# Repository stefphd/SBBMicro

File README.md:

# Introduction

This repository contains the source code for the self-balancing-bike micro-controller unit (Teensy 4.1-based 🚀️).
The introduction shows the files and folders contained in this repository and how they are organized, the prerequisites necessary, and the procedures to be used in order to build and upload the code, to generate the documentation, and to automatically generate the control-algorithm code from the Simulink model (using matlab tools).

Windows is officially supported, although compilation is also implemented for Linux. MacOS is NOT supported. 

## Files

Files:

* `controlModel.slx`: control model implementation in Simulink
* `gencode.m`: MATLAB function for code generation from Simulink model
* `params.sldd`: Simulink parameters used in `controlModel.slx`
* `build_linux.sh`: build shell script for Linux
* `build_win.bat`: build shmell script for Windows
* `Doxyfile`: configuration file for documentation generation from source code using *doxygen*
* `Makefile`: makefile for building, uploading and documentation generation using *make*
* `startup.m`: startup file for MATLAB (just to add necessary path)
* `INSTALL_PREREQ.md`: guide for the installation of the pre-requisites
* `README.md`: readme file

Code folders:

* `./include`: contains `.h` files included in source code
* `./src`: contains source `.c` or `.cpp` files, including main file `main.cpp`
* `./lib`: contains a folder for each used library, with file `library.properties` for defining the library properties (mandatory for arduino compiling) and `.h` and `.cpp` files (possibly contained in folder `./src/`)
* `./tools/teensy`: contains the core code for the Teensy microcontroller

Additional folders:

* `./tools/teensy-windows`: build tools for Windows
* `./tools/teensy-linux`: build tools for Linux
* `./docs/html`: contains the documentation in html (generated automatically from source code using *doxygen*)
* `./docs/extra`: contains extra documentation (user-written), which is included using *doxygen*
* `./matlab-tools`: contains matlab tools usefull for code generation and other stuff
* `./hardware`: contains the kicad project files
* `./.vscode`: contains VS code property file(s)
* `./.build` and `.cache`: hidden folders created only during compilation

## Pre-requisites

* *MATLAB/Simulink* with the *Embedded Coder Toolbox* installed (>=2021a), for control algorithm code generation only

No other dependecies are necessary: all used libraries are already included in `./lib/`.

Additional utilities (only recommended):

* *make* to build using the `Makefile`; alternativelly, shell or MATLAV scripts can be used
* *Visual Studio Code* with *C/C++* extension for code completation
* *Doxygen* to generate the documentation
* *KiCad* to open the schematic files in `./hardware`

See the installation guide for the pre-requisites for details.

## Documentation

Documentation for the source code and the user-defined libraries (but not for other third-party libraries) can be generated from the source using *Doxygen* with

```bash
doxygen
```

or using *make*

```bash
make doc
```

Generated documentation includes only a html version in `./docs/html`, with main file `index.html`. Documentation is also available on <https://stefphd.github.io/SBBMicro/>.
A latex documentation may be also generated by setting

```doxygen
GENERATE_LATEX  = YES
```

in `Doxyfile`. The latex version will be in `./docs/latex`, and can be compiled using latex with

```bash
cd ./docs/latex
make
```

which generates the pdf file `./doc/latex/refman.pdf`.

\attention Latex documentation requires having both *latex* and *make* installed.

## Code generation

Code generation of the control algorithm is performed via *MATLAB/Simulink* with the *Embedded Coder Toolbox*. Other toolboxes may be required. Code generation can be launch with *MATLAB* using

```MATLAB
startup;
gencode
```

The general usage of this function is

```MATLAB
startup;
gencode(modelname,dest_dir);
```

where `modelname` is the name of the Simulink model (without the `*.slx` extension included), while `dest_dir` is the destination directory: generated code is placed in `./dest_dir/modelname/src`. If no modelname is given, the function uses the first `*.slx` file found in the current directory. If no destination directory is given, the functions uses `./lib`. Code generation may be also performed using *make*, however this may take some time.

\note Toolboxes required by the code generation can be shown by running in MATLAB

```MATLAB
startup;
check_toolbox();
```

\attention For a correct usage in this project the above functions should be run in the main directory, and not in `./matlab-tools/`.

## Building

Compilation is performed using the *arduino-builder*. Bash scripts provide simple usage depending on the operative system:

* Linux:
  
  ```bash
  ./build_linux.sh
  ```
  
  or
  
  ```bash
  bash build_linux.sh
  ```
  
  \note Tested with Arch-Linux x64.

* Windows:
  
  ```bash
  ./build_win.bat
  ```
  
  \note Tested with Windows 10 x64.

* MacOS: not implemented yet, however it should be similar to Linux.

Alternatively, one can use `ctrl+shift+B` to build the code in *Visual Studio Code* with both Linux and Windows (this makes use of `build_linux.sh` or `build_win.sh` depending on the operative system). One may also use *make* the building and uploading.

\note The above shell scripts perform both the building and the uploading: it is not possible to build or upload only.

## Make tools

One may also use *make* for the building, uploading and the documentation generation. This allows several operations using similar syntax, so as to perform single operations at a time:

* `make` or `make all` to build and upload the code.
* `make build` to build the code only
* `make upload` to upload code only
* `make clean` to clean the build and cache directories
* `make remake` to clean, build and upload the code
* `make rebuild` to clean and rebuild
* `make doc` to build the documentation
* `make cleandoc` to clean the documentation
* `make help` to print the Makefile help

\note The above commands can be also used at the same time, e.g. `make build doc` to build and generate the documentation.

## MATLAB make

As an alternative to `make` and `gencode`, the code generation, buiding, uploading and documentation generation may be also performed at the same time from within the MATLAB command window. This employs a MATLAB function name `make` in `./matlab-tool/`. The function must be used inside MATLAB with the following syntax:

* `make all` or just `make` to generate code from the Simulink model, build and upload

* `make gencode` to generate the code only from the Simulink model. Note that this corresponds to call `gencode` with no input arguments, i.e. the first `*.slx` file found is used

* `make build` to build the code

* `make upload` to upload the code

* `make clean` to clean the build and cache directories

* `make remake` to clean, build and upload the code

* `make rebuild` to clean and rebuild

* `make doc` to build the documentation

* `make cleandoc` to clean the documentation

* `make help` to print the help.

\note Note that this function emulates the function `gencode` and the standard `make` commands. However, it does not require having `make` installed but only `doxygen` for the generation of the documentation.

\note The above commands can be also used at the same time, e.g. `make build doc` to build and generate the documentation.

## Known issues

* Undefined identifiers found by Visual Studio Code, however this is only a C/C++ IntelliSense issue (compilation works fine)

\todo Doc: Documentaton for Simuling and code generation???
\todo Make Arduino functions working in Simulink when compiling (maybe declare Arduino functions as external in Simulink, so as the linker links them)
\todo To implement brake motor

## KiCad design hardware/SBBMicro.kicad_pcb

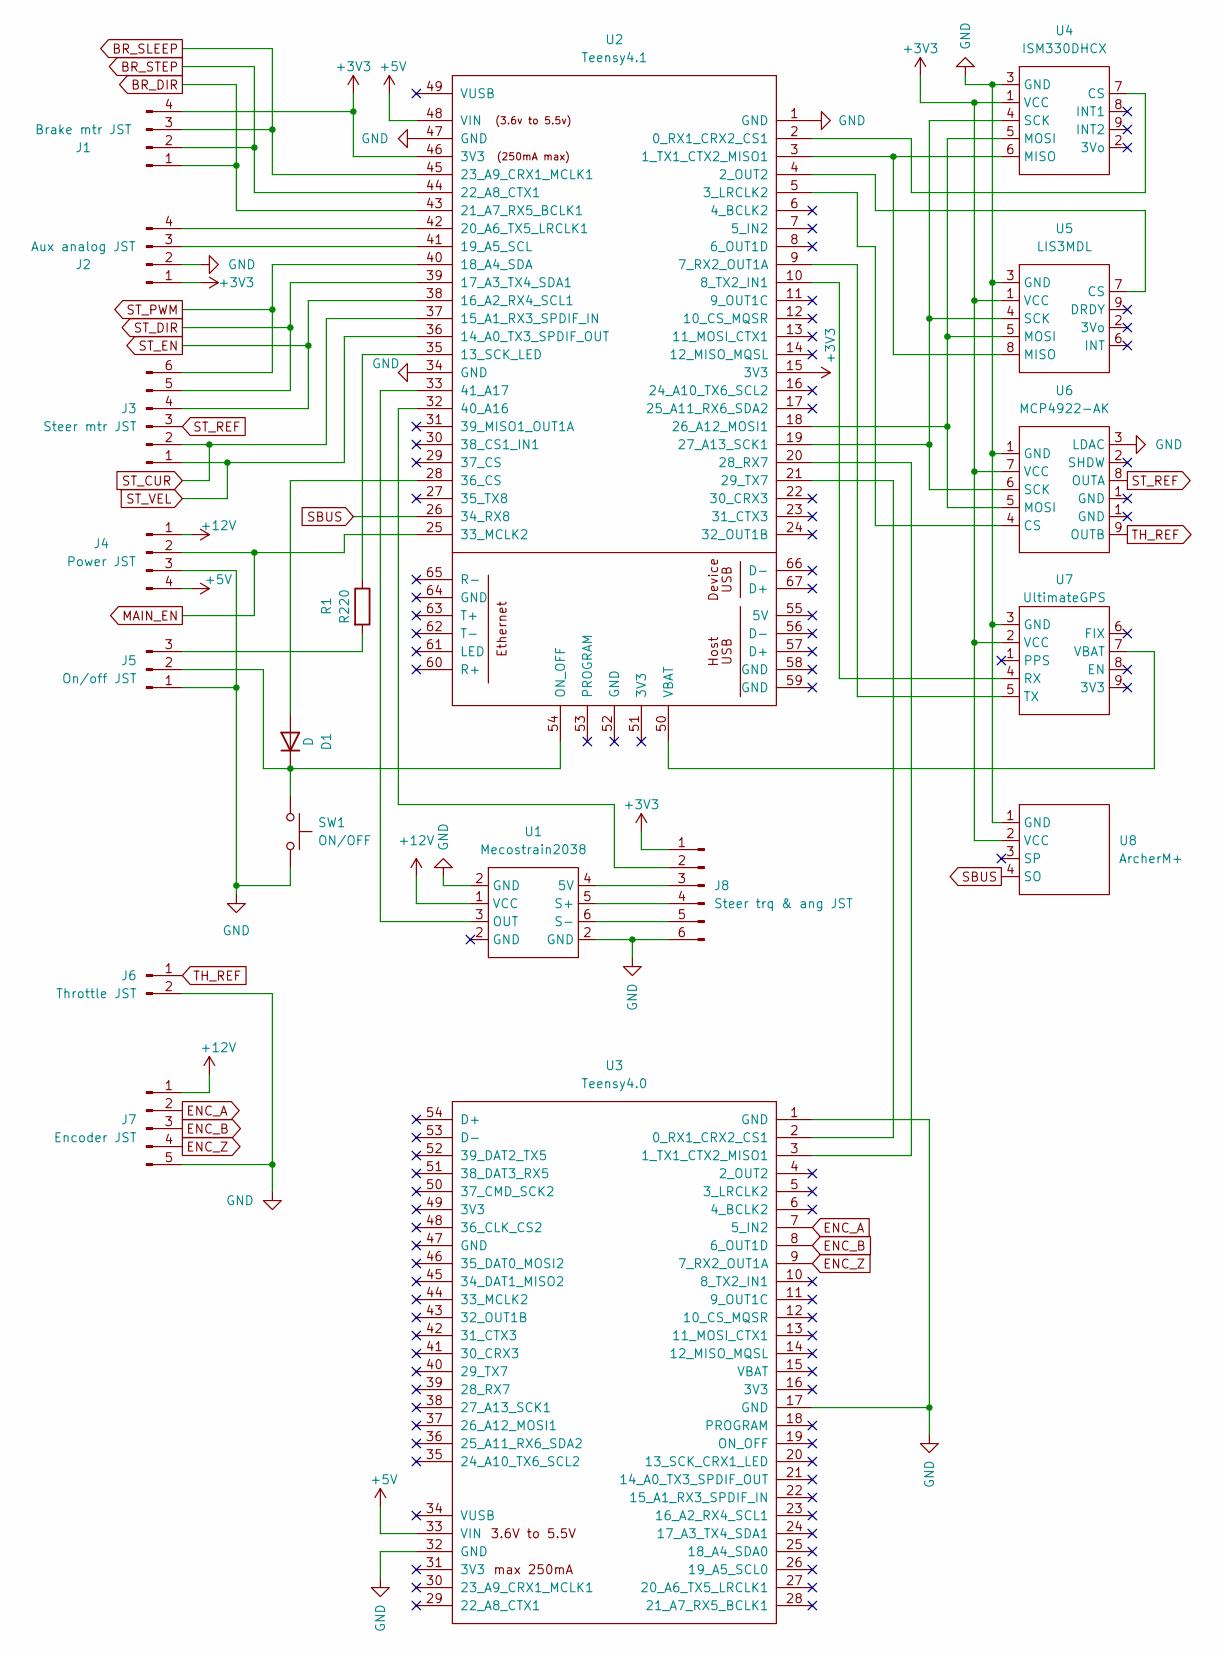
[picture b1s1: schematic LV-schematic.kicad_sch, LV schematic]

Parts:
D1: D; D_DO-34_SOD68_P7.62mm_Horizontal
J1: Brake mtr JST; JST_1x04_P2.54
J2: Aux analog JST; JST_1x04_P2.54
J3: Steer mtr JST; JST_1x06_P2.54
J4: Power JST; JST_1x04_P2.54
J5: On/off JST; JST_1x03_P2.54
J6: Throttle JST; JST_1x02_P2.54
J7: Encoder JST; JST_1x05_P2.54
J8: Steer trq & ang JST; JST_1x06_P2.54
R1: R220; R_Axial_DIN0204_L3.6mm_D1.6mm_P5.08mm_Horizontal
SW1: ON/OFF; SW_PUSH_6mm
U1: Mecostrain2038; Mecostrain-2038
U2: Teensy4.1; Teensy41
U3: Teensy4.0; Teensy40
U4: ISM330DHCX
U5: LIS3MDL
U6: MCP4922-AK
U7: UltimateGPS; Ultimate-GPS
U8: ArcherM+; JST_1x04_P2.54

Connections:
+3V3: J1.4, J2.1, J8.1, U2.15 (3V3), U2.46 (3V3), U3.16 (3V3), U3.33 (VIN), U4.1 (VCC), U5.1 (VCC), U6.7 (VCC), U7.2 (VCC), U8.2 (VCC)
+5V: J4.4, U2.48 (VIN)
+12V: J4.1, J7.1, U1.1 (VCC)
BR_DIR: J1.1, U2.43 (21_A7_RX5_BCLK1); also elsewhere on the board
BR_SLEEP: J1.3, U2.45 (23_A9_CRX1_MCLK1); also elsewhere on the board
BR_STEP: J1.2, U2.44 (22_A8_CTX1); also elsewhere on the board
ENC_A: J7.2, U3.7 (5_IN2)
ENC_B: J7.3, U3.8 (6_OUT1D)
ENC_Z: J7.4, U3.9 (7_RX2_OUT1A)
MAIN_EN: J4.2, U2.25 (33_MCLK2); also elsewhere on the board
unnamed: D1.1 (K), J5.2, SW1.1, U2.54 (ON_OFF)
unnamed: D1.2 (A), U2.28 (36_CS)
unnamed: J5.3, R1.2
unnamed: J8.2, U2.32 (40_A16)
unnamed: J8.3, U1.4 (5V)
unnamed: J8.4, U1.5 (S+)
unnamed: J8.5, U1.6 (S-)
unnamed: R1.1, U2.35 (13_SCK_LED)
unnamed: U1.3 (OUT), U2.33 (41_A17)
unnamed: U2.2 (0_RX1_CRX2_CS1), U4.7 (CS)
unnamed: U2.3 (1_TX1_CTX2_MISO1), U4.6 (MISO), U5.8 (MISO)
unnamed: U2.4 (2_OUT2), U5.7 (CS)
unnamed: U2.5 (3_LRCLK2), U6.4 (CS)
unnamed: U2.9 (7_RX2_OUT1A), U7.5 (TX)
unnamed: U2.10 (8_TX2_IN1), U7.4 (RX)
unnamed: U2.18 (26_A12_MOSI1), U4.5 (MOSI), U5.5 (MOSI), U6.5 (MOSI)
unnamed: U2.19 (27_A13_SCK1), U4.4 (SCK), U5.4 (SCK), U6.6 (SCK)
unnamed: U2.20 (28_RX7), U3.3 (1_TX1_CTX2_MISO1)
unnamed: U2.21 (29_TX7), U3.2 (0_RX1_CRX2_CS1)
unnamed: J2.3, U2.41 (19_A5_SCL)
unnamed: J2.4, U2.42 (20_A6_TX5_LRCLK1)
unnamed: U2.50 (VBAT), U7.7 (VBAT)
SBUS: U2.26 (34_RX8), U8.4 (SO)
ST_CUR: J3.2, U2.37 (15_A1_RX3_SPDIF_IN); also elsewhere on the board
ST_DIR: J3.5, U2.39 (17_A3_TX4_SDA1); also elsewhere on the board
ST_EN: J3.4, U2.38 (16_A2_RX4_SCL1); also elsewhere on the board
ST_PWM: J3.6, U2.40 (18_A4_SDA); also elsewhere on the board
ST_REF: J3.3, U6.8 (OUTA); also elsewhere on the board
ST_VEL: J3.1, U2.36 (14_A0_TX3_SPDIF_OUT); also elsewhere on the board
TH_REF: J6.1, U6.9 (OUTB)

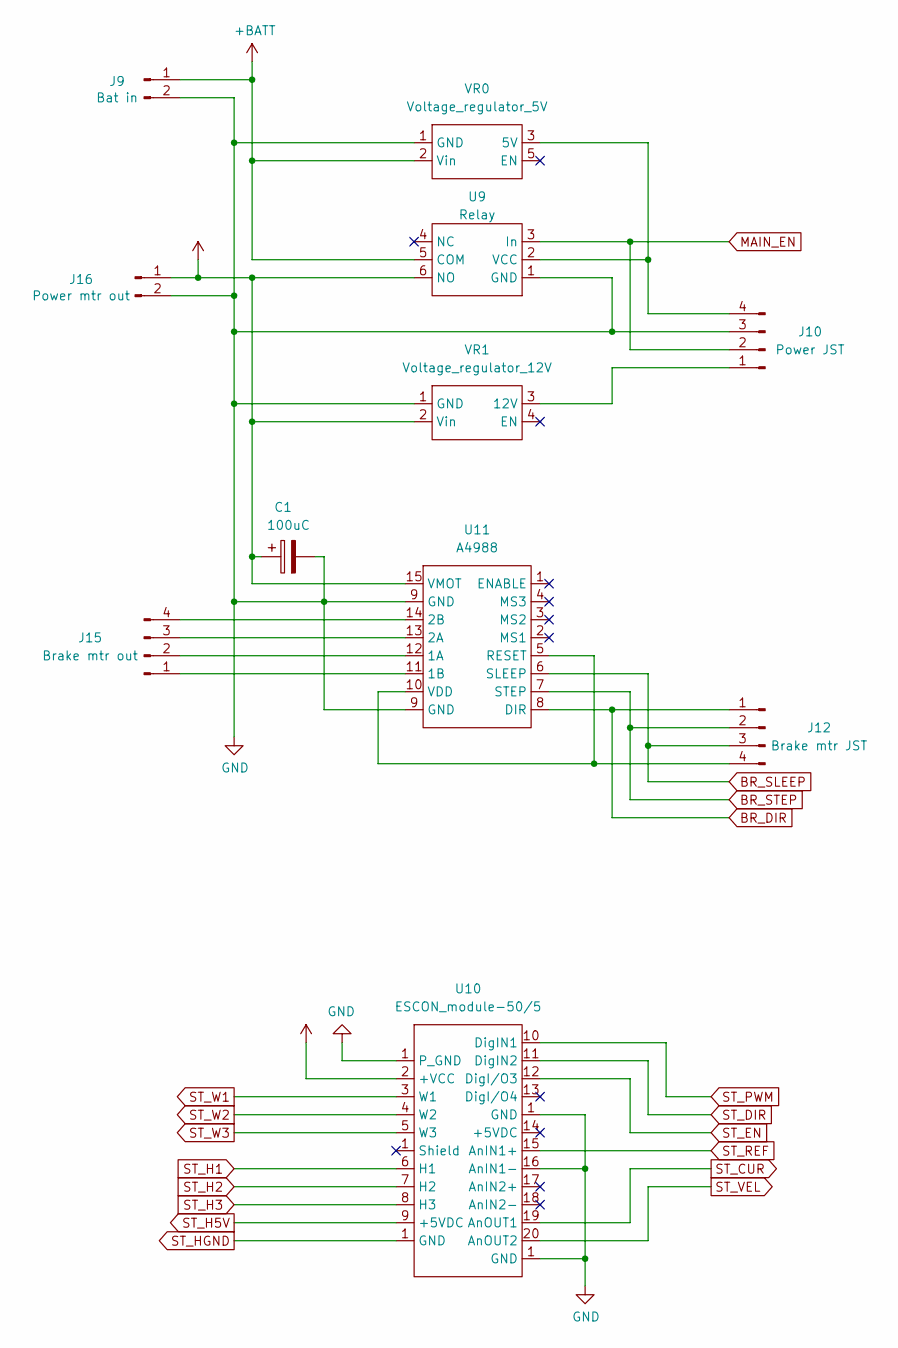
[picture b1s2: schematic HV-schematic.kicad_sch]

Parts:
C1: 100uC; CP_Radial_D5.0mm_P2.50mm
J9: Bat in; TerminalBlock_bornier-2_P5.08mm
J10: Power JST; JST_1x04_P2.54
J12: Brake mtr JST; JST_1x04_P2.54
J15: Brake mtr out; JST_1x04_P2.54
J16: Power mtr out; TerminalBlock_bornier-2_P5.08mm
U9: Relay
U10: ESCON_module-50/5; Escon module-50-5
U11: A4988
VR0: Voltage_regulator_5V; Voltage-reg_5V
VR1: Voltage_regulator_12V; Voltage-reg_12V

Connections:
+24V: C1.1, J16.1, U9.6 (NO), U10.2 (+VCC), U11.15 (VMOT), VR1.2 (Vin)
+BATT: J9.1, U9.5 (COM), VR0.2 (Vin)
BR_DIR: J12.1, U11.8 (DIR); also elsewhere on the board
BR_SLEEP: J12.3, U11.6 (SLEEP); also elsewhere on the board
BR_STEP: J12.2, U11.7 (STEP); also elsewhere on the board
MAIN_EN: J10.2, U9.3 (In); also elsewhere on the board
unnamed: J10.1, VR1.3 (12V)
unnamed: J10.4, U9.2 (VCC), VR0.3 (5V)
unnamed: J12.4, U11.5 (RESET), U11.10 (VDD)
unnamed: J15.1, U11.11 (1B)
unnamed: J15.2, U11.12 (1A)
unnamed: J15.3, U11.13 (2A)
unnamed: J15.4, U11.14 (2B)
ST_CUR: U10.19 (AnOUT1); also elsewhere on the board
ST_DIR: U10.11 (DigIN2); also elsewhere on the board
ST_EN: U10.12 (DigI/O3); also elsewhere on the board
ST_H1: U10.6 (H1)
ST_H2: U10.7 (H2)
ST_H3: U10.8 (H3)
ST_H5V: U10.9 (+5VDC)
ST_PWM: U10.10 (DigIN1); also elsewhere on the board
ST_REF: U10.15 (AnIN1+); also elsewhere on the board
ST_VEL: U10.20 (AnOUT2); also elsewhere on the board
ST_W1: U10.3 (W1)
ST_W2: U10.4 (W2)
ST_W3: U10.5 (W3)

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
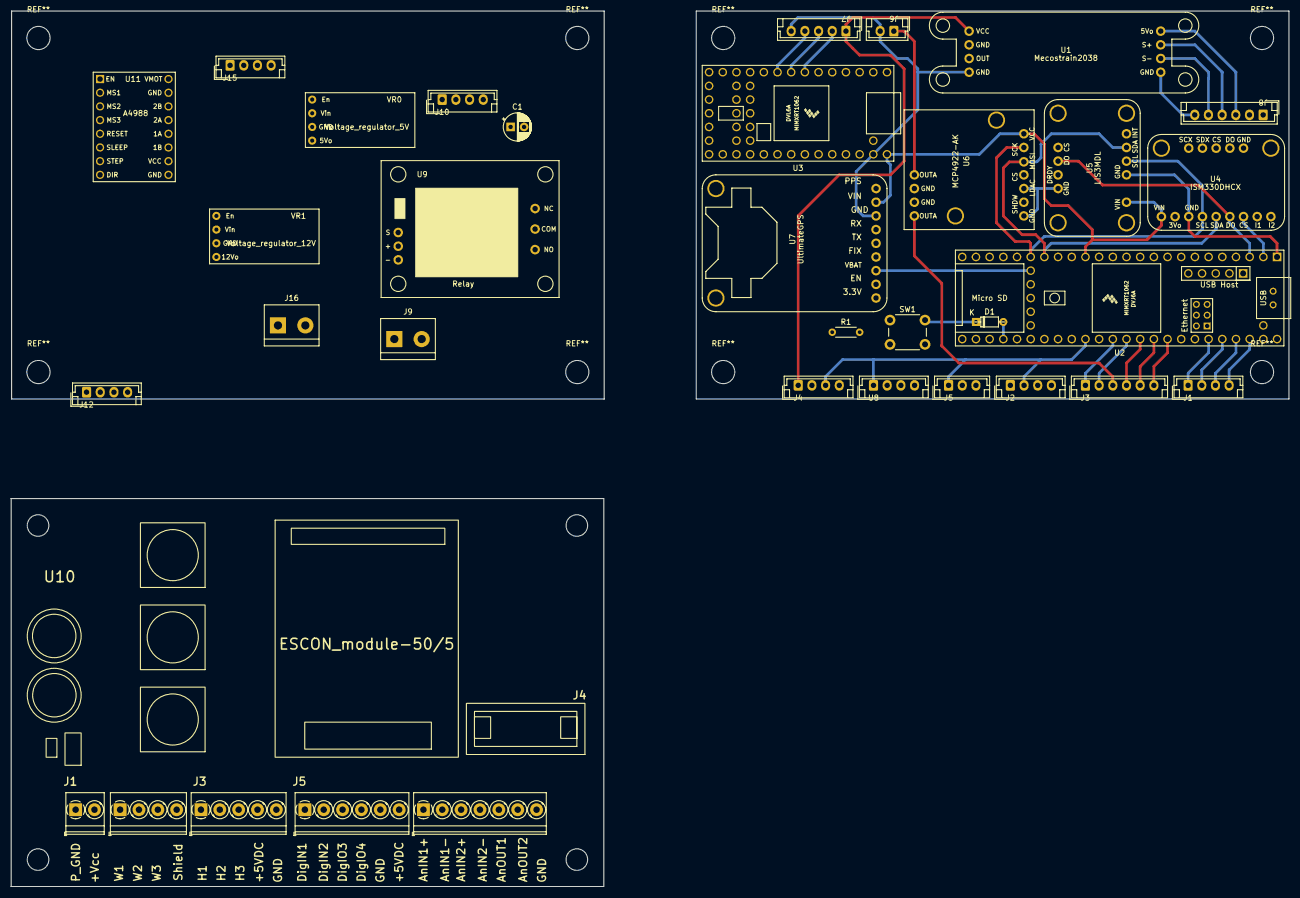
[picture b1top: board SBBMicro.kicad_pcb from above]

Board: 2 copper layers, 237.2 x 162.5 mm, 30 parts (0 on the bottom side), 50 nets.

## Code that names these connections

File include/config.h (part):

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#define BAUD_GPS_DEF	9600 //!< Default baudrate of GPS sensor (for init only).
#define BAUD_GPS		57600 //!< Actual baudrate of GPS sensor.
#define GPS_EXTBUFSIZE	128 //!< Extra buffer size for GPS sensor UART.
#define UART_SBUS		Serial8 //!< Used UART for SBUS communication. /details The UART used for the SBUS receiver. This runs with a baudrate of 100000. Initialization and setting is performed by the SBUS library.

//ADC
#define ADC_RES			12 //!< ADC resolution (in bits).
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#define MTR_EN_PIN		16 //!< Digital out for motor enable.
#define MTR_DIR_PIN		17 //!< Digital out for motor direction.
#define RELAY_EN_PIN	33 //!< Digital out for relay enable.
#define BR_DIR_PIN		21 //!< Digital out for brake motor direction.
#define BR_STEP_PIN		22 //!< Digital out for brake motor step.
#define BR_SLEEP_PIN	23 //!< Digital out for brake motor sleep.

//DIGITAL IN 
#define ONOFF_STATE_PIN	36 //!< Digital in for on/off buttun state (diode between onoff and this).
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#define SPEED_SAMPLING_FAC	1 //!< Sampling factor of speed sensor (expressed in units of #SAMPLING_TIME). \note This is the rate at which the sensor is read, not its output data rate. \warning Not used now. Speed sensor is read as fast as possible. \see SAMPLING_TIME
#define IMU_SAMPLING_FAC	1 //!< Sampling factor of IMU (expressed in units of #SAMPLING_TIME). \note This is the rate at which the sensor is read, not its output data rate (i.e. #ACC_ODR or #GYRO_ODR). \see SAMPLING_TIME ACC_ODR GYRO_ODR
#define MAG_SAMPLING_FAC	5 //!< Sampling factor of magnetometer (expressed in units of #SAMPLING_TIME). \note This is the rate at which the sensor is read, not its output data rate (i.e. #MAG_ODR). \see SAMPLING_TIME MAG_ODR
#define SBUS_SAMPLING_FAC	14 //!< Sampling factor of the SBUSr receiver. \note This is the rate at which the sensor is read, not its output data rate. \warning Not used now. SBUS is read as fast as possible. \see SAMPLING_TIME
#define DEF_LED 			2500 //!< Sampling factor of led in default mode (expressed in units of #SAMPLING_TIME). \see SAMPLING_TIME LedMode::DEF
#define LOG_LED 			500 //!< Sampling factor of led in log mode (expressed in units of #SAMPLING_TIME). \see SAMPLING_TIME LedMode::LOG
#define MTP_LED 			250 //!< Sampling factor of led in mtp mode (expressed in units of #SAMPLING_TIME). \see SAMPLING_TIME LedMode::MTP
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#define GYROZ_OFFSET    -0.0080F/GYRO_SCALE //!< Offset of gyro z. \details Value from offset calibration of the IMU.

//SBUS
#define NUM_CH_SBUS		7 //!< Number channels from SBUS. \details Number of the stored channel from the SBUS. \see RemoteCtrl
#define MAX_SBUS		1811 //!< Maximum value from SBUS. \details Maximum value received by the SBUS.
#define MIN_SBUS		172 //!< Minimum value from SBUS. \details Minimum value received by the SBUS.
#define ZERO_SBUS		992 //!< Zero-value for SBUS. \details Value corresponding to zero for the SBUS. This is hust the average of #MAX_SBUS and #MIN_SBUS. \see MAX_SBUS MIN_SBUS
#define TRESHOLD_LOGIC_SBUS	1400 //!< Treshold for SBUS logic channels. \details Treshold value for logic state received by the SBUS. If greaten than this value, it is a high state. \attention This value should be larger than #ZERO_SBUS, in order to recognize it as a low state. \see ZERO_SBUS
#define TRESHOLD_POS_SBUS	1400 //!< Treshold for positive value. \details Treshold value for positive state received by the SBUS. If greaten than this value, it is a +1.
#define TRESHOLD_NEG_SBUS	600 //!< Treshold for negative value. \details Treshold value for positive state received by the SBUS. If lower than this value, it is a -1.
#define MAX_MISSING_SBUS	10*SBUS_SAMPLING_FAC //!< Maximum missing packets for SBUS. \details Maximum missing packets for the SBUS communication. \note Check for missing packet is performed avery #SAMPLING_TIME milliseconds. \see SAMPLING_TIME
#define MAX_REF_INPUT1	1.0F //!< Maximum value for input reference 1. \details Maximum value for the input reference in the control model. Signals from SBUS (int16_t) are remapped within #MIN_SBUS and #MAX_SBUS as float numbers. \see MIN_SBUS MAX_SBUS CONVERT_CHANNEL_TO_FLOAT
#define MIN_REF_INPUT1	0.0F //!< Minimum value for input reference 1. \details Minimum value for the input reference in the control model.  Signals from SBUS (int16_t) are remapped within #MIN_SBUS and #MAX_SBUS as float numbers. \see MIN_SBUS MAX_SBUS CONVERT_CHANNEL_TO_FLOAT
#define MAX_REF_INPUT2	1.0F //!< Maximum value for input reference 2. \details Maximum value for the input reference in the control model. Signals from SBUS (int16_t) are remapped within #MIN_SBUS and #MAX_SBUS as float numbers. \see MIN_SBUS MAX_SBUS CONVERT_CHANNEL_TO_FLOAT
#define MIN_REF_INPUT2	-1.0F //!< Minimum value for input reference 2. \details Minimum value for the input reference in the control model.  Signals from SBUS (int16_t) are remapped within #MIN_SBUS and #MAX_SBUS as float numbers. \see MIN_SBUS MAX_SBUS CONVERT_CHANNEL_TO_FLOAT
#define SBUS_THROTTLE_CH 1 //!< Throttle channel in SBUS. \details Channel of SBUS for throttle reference. \warning Channel number is one-based.
#define SBUS_ROLL_CH	2 //!< Roll channel in SBUS. \details Channel of SBUS for roll reference. \warning Channel number is one-based.
#define SBUS_EN_CH		5 //!< Enable channel in SBUS. \details Channel of SBUS for enable signal. \warning Channel number is one-based.
#define SBUS_PB_CH		6 //!< brake channel in SBUS. \details Channel of SBUS for brake signal. \warning Channel number is one-based.
#define SBUS_THR_OR		3 //!< Direct throttle channel in SBUS. \details Channel of SBUS for overrideing the throttle channel. \warning Channel number is one-based.
#define SBUS_SEL_CH		7 //!< 3 selector channel in SBUS. \warning Channel number is one-based.

//LIMITS
#define MAX_REFCUR		10 //!< Maximum reference current. \warning Must be consistent with that in ESCON studio and Simulink. 
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	\return The float value within MIN and MAX.
	\see MAX_SBUS MIN_SBUS
*/
#define CONVERT_CHANNEL_TO_FLOAT(X, XMIN, XMAX)	(float(X)-MIN_SBUS)/(MAX_SBUS-MIN_SBUS)*(XMAX-XMIN) + XMIN //macro for conversion of SBUS channels to floats

/*! \brief Convert brake lever position to motor steps.
	\details Macro for the conversion of the brake lever position (mm) to the number of steps of the steeper motor.
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#define BR_SLEEP_STATE  HIGH //!< Enable state for brake motor.
#define MTR_ENABLE		digitalWriteFast(MTR_EN_PIN, MTR_EN_STATE), delay(100) //!< Macro for motor enable. \see MTR_EN_PIN MTR_EN_STATE
#define RELAY_ENABLE	digitalWriteFast(RELAY_EN_PIN, RELAY_EN_STATE), delay(500) //!< Macro for relay enable. \see RELAY_EN_PIN RELAY_EN_STATE
#define BR_ENABLE 		digitalWriteFast(BR_SLEEP_PIN, BR_SLEEP_STATE) //!< Macro for brake motor enable. \see BR_SLEEP_PIN BR_SLEEP_STATE
#define BR_DISABLE 		digitalWriteFast(BR_SLEEP_PIN, !BR_SLEEP_STATE) //!< Macro for brake motor enable. \see BR_SLEEP_PIN BR_SLEEP_STATE
#define LEDON			digitalWriteFast(LED_BUILTIN, HIGH) //!< Macro for LED on. \details Standard value for LED_BUILTIN is 13 in the Arduino environment.
#define LEDOFF			digitalWriteFast(LED_BUILTIN, LOW) //!< Macro for LED off. \details Standard value for LED_BUILTIN is 13 in the Arduino environment.

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
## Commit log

2022-02-10 Linux permission denied issue fixed
2022-02-21 Add libraries
    Necessary (external) libraries added
2022-02-21 Add include files
    Necessary include files added
2022-02-21 Add MATLAB/Simulink file
    MATLAB/Simulink file for control model code generation added
2022-02-21 Remove platformIO files
2022-02-21 Add generated code for control model
    Generated code of control model using Simulink Enbedeed Coder added
2022-02-21 Create build_linux
2022-02-21 Create makefile
2022-02-21 Update makefile
2022-02-21 Add MTP library
2022-02-21 Update include files
2022-02-21 Add teensy core and hardware
2022-02-21 Remove unnecessary libraries
    Unnecessary libraries removed and used (built-in) libraries moved to lib/
2022-02-21 Remove unnecessary libraries from hardware/
2022-02-21 Add do_led()
    do_led() function for status LED added
2022-02-22 Update platform.txt
    platform.txt modified to change with the operative system used (use tools-windows or tools-linux depending on the OS)
2022-02-22 Remove hardware/tools
    hardware/tools replaced will be replaced by hardware/tools-windows and hardware/tools-linux depending on the OS
2022-02-22 Add hardware/tools-linux
    hardware/tools-linux added for compiling in linux
2022-02-22 Add hardware/tools-windows
    hardware/tools-windows added for compiling in windows
2022-02-22 Update README.md
    File & folder information added, TODO list added
2022-02-22 Update README.md
    Typo fixed
2022-02-22 Add teensy_loader_cli.exe
    Binaries of Tensy loader for Windows x64 added (compiled using MSYS2)
2022-02-22 Update build_win.bat
    Uploading hex file using teensy_loader_cli added
2022-02-22 Create prototypes.h
    Create prototypes.h to declare all functions before their implementation
2022-02-22 Create tasks.json
    tasks.json created for building of code in VS code using ctrl+shift+B. Proper building shell script will be run depending on the OS
2022-02-22 Update README.md
    README file updated with information on building using VS code
2022-02-23 Update include.h
    Made it clear
2022-02-23 Add GPS speed in controlModel input
2022-02-23 Update include.h
    Typo fixed
2022-03-01 Update logger.h
    Log at 1kHz
2022-03-01 Update README.md
    Add MTP mode usage in both Windows and Linux
2022-03-01 Update debug.h
    Add timing to debug stuff
2022-03-09 add sbus library
2022-03-09 Update main.cpp
    Add serial flush
2022-03-09 sbus library updated with SL mods
2022-03-09 serial_flush added
2022-03-09 include sbus library
2022-03-09 notes added - to change ONOFF_STATE_PIN to 36
2022-03-10 sbus library added
2022-03-15 First commit of documentation
2022-03-16 Add documentation
2022-03-17 Update sbus.h
    failsafe_ and lost_frame_ initialized to true (for possible missing values at the beggining). ch(int16_t*) and ch(int16*, len) added in SL_MOD version.
2022-03-17 Update config.h
    Configurations for SBUS added
2022-03-17 Update objects.h
    Types and object for SBUS added
2022-03-17 Remove doc folder
2022-03-17 docs folder instead of doc
2022-03-17 Update Doxyfile
    sub doc with docs
2022-03-17 Add SBUS stuff
2022-03-17 Dark theme doc
2022-03-17 Doc deleted
2022-03-17 Add docs
2022-03-18 Remove darkmode in docs
2022-03-18 Revert "Remove darkmode in docs"
    This reverts commit d5472c3890c3957315ce68cd81f913eb3c3c7be8.
2022-03-18 deploy: 60dface9e417306396f949073b01c7e41ae3f178
2022-03-18 Update doc
2022-03-18 deploy: 547f01660def01039af643dafaf4f15697f5409f
2022-03-18 Make uploading working
2022-03-18 deploy: f2cb363cd2949a35fe777a6234a900b21e2d39d5
2022-03-18 Add Makefile
    Makefile with several operations added. See "Make" section in README
2022-03-18 deploy: f8e9c7a9f7f590cb5b3ae34c8e8dd314eaca180c
2022-03-18 Remove teensy3 from core
    teeensy3 is not used, remove it
2022-03-18 deploy: ef1a5b65e6f6387d4fb23fcafdaabc2b231a9e9e
2022-03-18 Fix typo
2022-03-18 Fix typos
2022-03-18 Remove loop() and setup()
    User-defined main() used instead of loop() and setup() (employed in Arduino workflow)
2022-03-18 deploy: d93822bd2df3a45fedda66401048b47eb6a2dd05
2022-03-18 deploy: 8a649cb11c661e8365659af0d165d86793027985
2022-03-22 Update build_win.bat
    Bug fixed
2022-03-22 Update control model
    Reference inputs added to control model
2022-03-22 deploy: b47ed67e59371ed1cf9e0fa158e74f59a18537cb
2022-03-22 Update control model
    Typo fixed in gencode()
2022-03-22 Add ref inputs
2022-03-22 deploy: 09dce47418fe1f7a20d6664afb869e7c1038be2f
2022-03-22 Typo fixed
2022-03-22 deploy: d9641c955ae2c5873eaec4142767473e507a0bbf
2022-03-22 Update control
2022-03-22 SBUS channel defines added
2022-03-22 Update docs
2022-03-22 deploy: 6f8f9076d96a8a6b8507abf7ca54cf6d0cafa29e
2022-03-23 Update control mode
2022-03-23 Update control model
2022-03-25 deploy: ae96da121a132ebf0ac865b5c81a01c4572ea242
2022-03-26 deploy: 8381d573065de42ac89b32b7bb78b99a0b50d8ba
2022-04-04 Update Makefile
    Add Windows support
2022-04-04 Rename sbbmicro-icon.svg
2022-04-04 deploy: 2059079ca71e91957f5207cbb70e6cb37f521d63
2022-04-04 deploy: 974581f9666ff8ba4eb2e10861021ff2be756c05
2022-04-04 Update to MATLAB R2022a
2022-04-04 Update code generation
2022-04-04 deploy: b60d0a765ae5b7caaed9e96d0eadfa58b61a1396
2022-04-04 Update Makefile
    Add new rule 'gencode' for code generation
2022-04-04 deploy: 86faaa2fb6fcd2f08863ef1a899feb9e4b3f16b4
2022-04-04 Update Makefile
    Add help to makefile
2022-04-04 deploy: 4341cfb13a186c05e577621ac959b56b9e16d060
2022-04-05 Add check toolbox
2022-04-05 deploy: 2fe508691dbf4e23b04cec5adabc452baf45e780
2022-04-05 General update
2022-04-05 deploy: d6cd434f17ea554331ab4cd3dd8dd7fab2098faa
2022-04-05 deploy: 387685b3c1222865da628cb4a626e16b27175660
2022-04-05 Update gencode.m
    Set toolchain depending on the OS
2022-04-05 Update code gen
2022-04-05 Update gencode.m
    Fix typo
2022-04-05 deploy: 6e356b73f57d92a9f72330dfccb0d06c73c1c9f8
2022-04-06 Add matlab tools
2022-04-06 deploy: b88965c963cc15598cacb649405dcb69d9fa9beb
2022-04-06 Update check_toolbox.m
    Fix typo
2022-04-11 Add hw scheme
2022-04-11 deploy: ad8195bb74b9bd1766c45f76914857f6b5e518ab
2022-04-11 deploy: 6d2981611d22b2eebe2621b77d0162e2337183bf
2022-04-11 deploy: a0de02d91f05c26d7d5fad42321850a8aae42c30
2022-04-12 deploy: 435464416d11e2a60f41a2ef8dd83ad2e9025dd7
2022-04-13 deploy: 2daafb137d44bbe9f060b49892f9ffd51910e9e6
2022-04-13 Update lv schematics
2022-04-13 deploy: 1fcd9b9e3b4046d68d63a49849564544331c5d66
2022-04-13 deploy: 939ddbb86a98d273514d51076601918097e00af7
2022-04-13 deploy: 2c55a3b93692e35e0c26b2a56de0e3009557b55d
2022-04-13 deploy: 77bc4e8e6911632ef1a63ec0d0cbe6aef236c3bd
2022-04-13 Add kicad project
2022-04-13 deploy: a536cfdf0001de0b46ecdd6567c1d38fe46a3ca4
2022-04-13 deploy: a2edb6e018e10bec180a07fcd926581d23a967c5
2022-04-13 Update kicad
2022-04-14 Update kicad and doc
2022-04-14 deploy: 750227ee3604a2aeb58985f5dcd9059a1ddc7aca
2022-04-14 deploy: ad3a5b344f70e43f5da857557191e4729c446880
2022-04-20 Change directories
    ./hardware renamed to ./build-tools
    ./kicad renamed to ./hardware
2022-04-20 deploy: 4e2339fe915d10a8074b0212a3c732596770d95f
2022-04-20 Update shell scripts
2022-04-20 Add stepper library to ./lib
2022-04-20 Fix directory names
2022-04-20 Include teensystep4.h
2022-04-20 Fix bug
    Renamed arduino.h to Arduino.h to make compilation working
2022-04-20 deploy: 047d561a2f21ecb0e91b19fe0d6e72355fbe8241
2022-04-20 Change directory names
    build-tools changed to tools to make window compilation working
    hardware changed to schematics
2022-04-20 deploy: 86ba7ea09b87f8394fafa56df22d78b73fbb4c30
2022-04-20 Revert "Update TMR.h"
    This reverts commit f8765266713d74e7305b786ec78f2b09067ee717.
2022-04-20 Revert "Change directory names"
    This reverts commit 86ba7ea09b87f8394fafa56df22d78b73fbb4c30.
2022-04-20 deploy: 4024399304897e468067987906407c1d1fa76207
2022-04-20 Change directory names
2022-04-20 deploy: 205d33d1e3677b975cdef06cc4c11373f205c774
2022-04-20 Add brake motor
2022-04-20 deploy: 2dc595e24cde3a663bebcd221a86209cfb8cc682
2022-04-28 Fix brake motor issues
2022-04-28 deploy: 4ecb6cc4d17abc179661d47fc3e322537a622ad4
2022-05-18 Override remote enable duging debug
2022-05-18 deploy: bd6555092ebb0cf4d4430cb37e30c12e1ae57656
2022-05-26 Add and update docs
2022-05-26 Add set_ctrl_params function
2022-06-01 deploy: cdbdcf0ab0180d7bad4ca31a578346b489acc060
2022-06-06 deploy: 7274df97edabe85945d89062dbe9b1514419d834
2022-06-21 Add tests
2022-06-21 Remove doc
2022-06-21 deploy: 5f6068af9471657d7128884ce480f0f0c901fc2b
2022-06-21 Ignore doc
2022-06-23 Fix indentation
2022-06-23 Fix typo in exclude docs
2022-06-23 Remove gencode and checktoolbox rules
2022-06-23 Add matlab startup
2022-06-23 Update Doxyfile
2022-06-23 deploy: 159405d7dc45d0ca8fc998a4421ce40ce19bb349
2022-06-23 deploy: 45055cdaaafefe97bb6dd16adf12ff04a4a07c8a
2022-06-23 Bug fix for Windows
2022-06-24 Add extension .md
2022-06-24 Add HostPort-matlab
2022-06-24 Move HostPort-matlab to https://github.com/stefphd/HostPort-matlab
2022-07-12 deploy: d16f6102dc8395b46837ba08ca0ac04862780d5f
2022-07-12 Add constexpr for default header and terminator
2022-07-12 deploy: fed684fd0cff0ab8b0b54d3568cc0f5ccc9feda4
2022-09-13 Fix bug: missing set_ctrl_input() in main
2022-09-13 Add return after impulse test
2022-09-13 Update schematics
2022-09-13 Skip impulse test
2022-09-13 deploy: 8f0b9e69c816605679586054e814a8d0adea1ae3
2022-09-29 Add MATLAB make function to build inside MATLAB
2022-09-29 deploy: 2d8dcb8dcd86dab663aa65d4df471965e7477418
2022-10-06 Make MATLAB 'make' not dependent on 'make'
2022-10-06 deploy: a6c1332b7c8020e7347c5d4c8bdc24b2154efe00
2023-03-02 deploy: f1042d8bd29affc0a369488904805074cfd7870b
2023-07-20 Add EN_LONG_CTRL to disable longitudinal control
2023-07-20 Turn off warnings during compilation
2023-12-19 deploy: 2d7c3fcc6e1d9bb37ee41d2eddd0e50a89bcb214
2023-12-20 deploy: 79f6e86c357f046d0cdf8f9dc7d4177c17912021
2024-01-20 deploy: 96462e475a6eb276bf83df81e607ce03bfa73a62
2024-01-22 FIx typo.
2024-01-22 Add enable remote control to deactivate sbus
2024-01-22 deploy: d9d602352c258be1efa3fb8f54d60c6db70a41c5
2024-01-25 deploy: 9cfedb4bc55b9794ee8178be2aa14998ae8d1146
2025-06-03 Remove "...." in build script and update matlab ver
2025-06-03 deploy: 563d18e2ee9c52a948176d71140c383255504c2e
2025-06-03 deploy: e6433f24fbd6f5aa129a1893ab9bcbede6d6bbd6
2025-07-03 select toolchain automatically (not used)
2025-07-03 Update control lib
2025-07-03 Fix MATLAB make.m
2025-07-10 Add Windows Make
2025-07-10 Add SBB Test and other
2025-07-10 deploy: a48739ed6552fb5d9ba2b08f6a42ba4b36d4800e
2025-07-14 Change ref limits
2025-07-14 deploy: 5843d0633cea5f617f21b923c308fa32c3399331
2025-07-14 Make SBB test working (tested)
2025-07-14 deploy: 3203e155bb7cb965cfd92ddb2f526c0757966dee
2025-07-14 Add SE and SC switch to simulink inputs
2025-07-14 deploy: 7defdd29594e2a068b17cf8fa5f8cef5315685b4
2025-07-17 Add throttle test
2025-07-17 deploy: 99d9c5bfb1c011439d66f86b2656ff0ca2d3bbe0
2025-07-21 Add missing dll for make.exe
2025-07-21 Remove sbb test
2025-07-21 deploy: b6f9b4cda34bc293563c25dd5af8ab4d5c7f5786
2025-09-20 Change LED blinking
2025-09-20 deploy: 4871f9e99222e2662bcc21865d31c4bb4acfcc7a
2026-02-18 deploy: 2b9dac8dc298ef3271013396171eafb616545256
